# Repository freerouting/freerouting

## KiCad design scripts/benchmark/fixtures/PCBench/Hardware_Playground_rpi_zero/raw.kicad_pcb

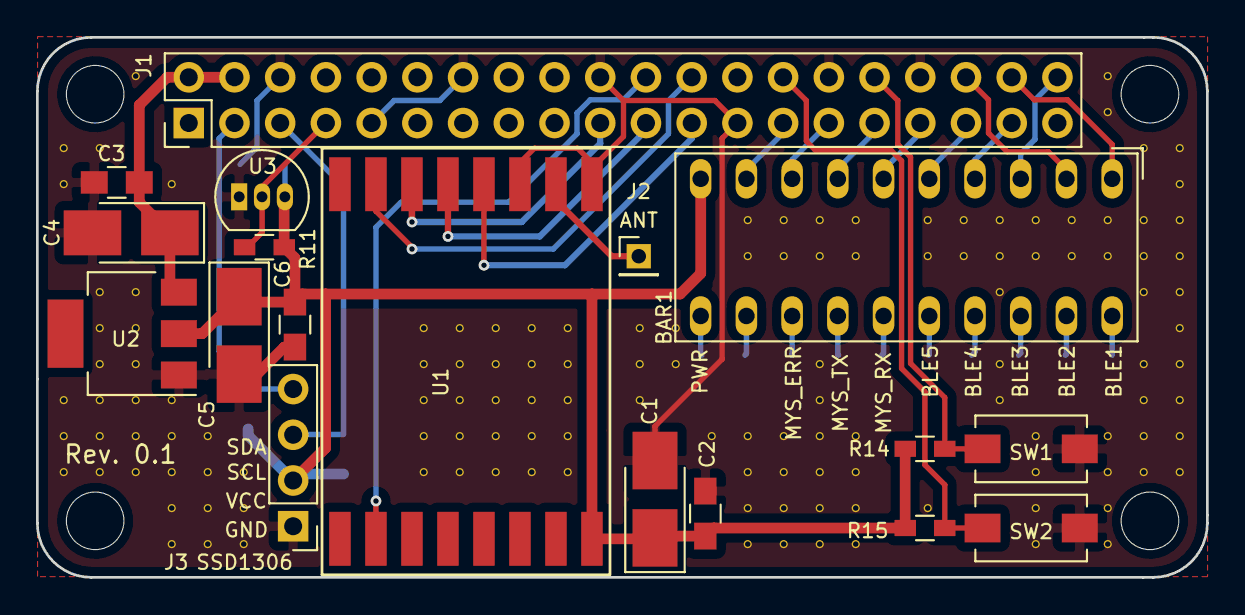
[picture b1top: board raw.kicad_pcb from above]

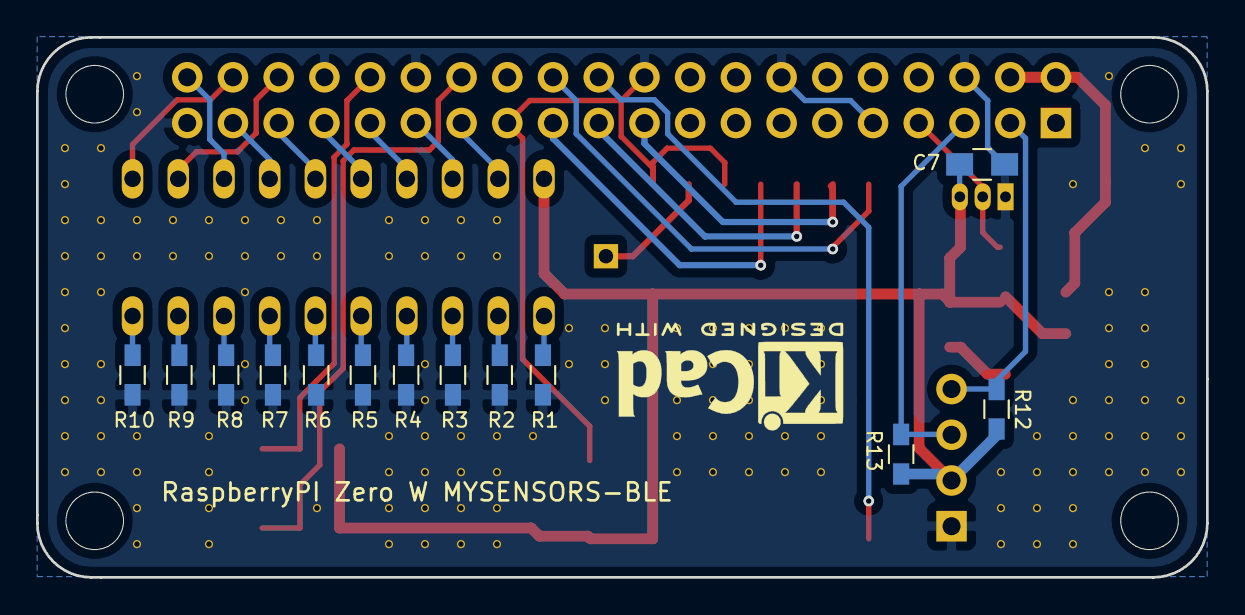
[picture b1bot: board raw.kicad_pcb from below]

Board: 2 copper layers, 65.0 x 30.0 mm, 164 parts (13 on the bottom side), 33 nets.

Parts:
BAR1: HDSP-4850_2; HDSP-4850
C1, C4, C5: 22u; CP_Tantalum_Case-B_EIA-3528-21_Hand
C2, C3, C6, C7: 100n; C_0805_HandSoldering
J1: RPI_Zero_W; Pin_Header_Straight_2x20_Pitch2.54mm
J2: ANT; Pin_Header_Straight_1x01_Pitch2.00mm
J3: SSD1306; Pin_Header_Straight_1x04_Pitch2.54mm
R1, R2, R3, R4, R5, R6, R7, R8, R9, R10: 220; R_0603_HandSoldering
R11, R12, R13: 4K7; R_0603_HandSoldering
R14, R15: 10K; R_0603_HandSoldering
SW1, SW2: BLE; SW_SPST_EVQPE1
U1: RFM69HW; RFM69HW_SMD_Handsoldering
U2: AMS1117; SOT-223
U3: DS18B20; TO-92_Inline_Narrow_Oval
V3_4, V3_5, V3_11, V3_12, V3_13, V4_4, V4_8, V4_9, V4_10, V4_11, V4_12, V4_13, V5_2, V5_8, V5_9, V5_10, V5_11, V5_12, V5_13, V6_5, V6_11, V6_12, V6_13, V6_14, V6_15, V7_12, V7_13, V7_14, V7_15, V8_13, V8_14, V8_15, V13_9, V13_10, V13_11, V13_12, V13_13, V14_9, V14_10, V14_11, V14_12, V14_13, V15_9, V15_10, V15_11, V15_12, V15_13, V16_9, V16_10, V16_11, V16_12, V16_13, V17_9, V17_10, V17_11, V17_12, V17_13, V19_9, V19_10, V19_11, V20_9, V20_10, V21_12, V22_6, V22_7, V22_12, V22_13, V22_14, V22_15, V23_6, V23_7, V23_12, V23_13, V23_14, V23_15, V24_6, V24_7, V24_10, V24_11, V24_12, V24_13, V24_14, V24_15, V25_6, V25_7, V25_12, V25_13, V25_14, V25_15, V27_6, V27_7, V27_14, V28_6, V28_7, V29_6, V29_7, V29_8, V29_10, V29_11, V30_6, V30_7, V30_12, V30_13, V30_14, V30_15, V31_6, V31_7, V32_2, V32_3, V32_6, V32_7, V32_12, V32_13, V32_14, V32_15, V33_4, V33_6, V33_7, V33_8, V33_10, V33_11, V33_12, V33_13, V34_4, V34_5, V34_6, V34_7, V34_8, V34_9, V34_10, V34_11, V34_12, V34_13: AUTO_VIA; VIA_MATRIX

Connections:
+3V3: BAR1.10, C1.1, C2.2, C5.1, C6.2, C7.1, J3.2, R11.1, R12.2, R13.2, R14.1, R15.1, U1.8, U2.2, U3.3
+5V: C3.2, C4.1, J1.2, J1.4, U2.3
/RFM69_CE: J1.22, U1.2
/RFM69_CS: J1.24, U1.15
/RFM69_MISO: J1.21, U1.13
/RFM69_MOSI: J1.19, U1.14
/RFM69_SCK: J1.23, U1.12
/SSD_SCL: J1.5, J3.3, R13.1
/SSD_SDA: J1.3, J3.4, R12.1
/SW1: J1.32, R14.2, SW1.1
/SW2: J1.28, R15.2, SW2.1
GND: C1.2, C2.1, C3.1, C4.2, C5.2, C6.1, C7.2, J1.6, J1.9, J1.14, J1.20, J1.25, J1.30, J1.34, J1.39, J3.1, R1.2, R2.2, R3.2, R4.2, R5.2, R6.2, R7.2, R8.2, R9.2, R10.2, SW1.2, SW2.2, U1.9, U1.11, U2.1, U3.1, V3_4.1, V3_5.1, V3_11.1, V3_12.1, V3_13.1, V4_4.1, V4_8.1, V4_9.1, V4_10.1, V4_11.1, V4_12.1, V4_13.1, V5_2.1, V5_8.1, V5_9.1, V5_10.1, V5_11.1, V5_12.1, V5_13.1, V6_5.1, V6_11.1, V6_12.1, V6_13.1, V6_14.1, V6_15.1, V7_12.1, V7_13.1, V7_14.1, V7_15.1, V8_13.1, V8_14.1, V8_15.1, V13_9.1, V13_10.1, V13_11.1, V13_12.1, V13_13.1, V14_9.1, V14_10.1, V14_11.1, V14_12.1, V14_13.1, V15_9.1, V15_10.1, V15_11.1, V15_12.1, V15_13.1, V16_9.1, V16_10.1, V16_11.1, V16_12.1, V16_13.1, V17_9.1, V17_10.1, V17_11.1, V17_12.1, V17_13.1, V19_9.1, V19_10.1, V19_11.1, V20_9.1, V20_10.1, V21_12.1, V22_6.1, V22_7.1, V22_12.1, V22_13.1, V22_14.1, V22_15.1, V23_6.1, V23_7.1, V23_12.1, V23_13.1, V23_14.1, V23_15.1, V24_6.1, V24_7.1, V24_10.1, V24_11.1, V24_12.1, V24_13.1, V24_14.1, V24_15.1, V25_6.1, V25_7.1, V25_12.1, V25_13.1, V25_14.1, V25_15.1, V27_6.1, V27_7.1, V27_14.1, V28_6.1, V28_7.1, V29_6.1, V29_7.1, V29_8.1, V29_10.1, V29_11.1, V30_6.1, V30_7.1, V30_12.1, V30_13.1, V30_14.1, V30_15.1, V31_6.1, V31_7.1, V32_2.1, V32_3.1, V32_6.1, V32_7.1, V32_12.1, V32_13.1, V32_14.1, V32_15.1, V33_4.1, V33_6.1, V33_7.1, V33_8.1, V33_10.1, V33_11.1, V33_12.1, V33_13.1, V34_4.1, V34_5.1, V34_6.1, V34_7.1, V34_8.1, V34_9.1, V34_10.1, V34_11.1, V34_12.1, V34_13.1
unnamed: BAR1.1, J1.38
unnamed: BAR1.2, J1.36
unnamed: BAR1.3, J1.40
unnamed: BAR1.4, J1.37
unnamed: BAR1.5, J1.35
unnamed: BAR1.6, J1.33
unnamed: BAR1.7, J1.31
unnamed: BAR1.8, J1.29
unnamed: BAR1.9, J1.27
unnamed: BAR1.11, R1.1
unnamed: BAR1.12, R2.1
unnamed: BAR1.13, R3.1
unnamed: BAR1.14, R4.1
unnamed: BAR1.15, R5.1
unnamed: BAR1.16, R6.1
unnamed: BAR1.17, R7.1
unnamed: BAR1.18, R8.1
unnamed: BAR1.19, R9.1
unnamed: BAR1.20, R10.1
unnamed: J1.7, R11.2, U3.2
unnamed: J2.1, U1.10

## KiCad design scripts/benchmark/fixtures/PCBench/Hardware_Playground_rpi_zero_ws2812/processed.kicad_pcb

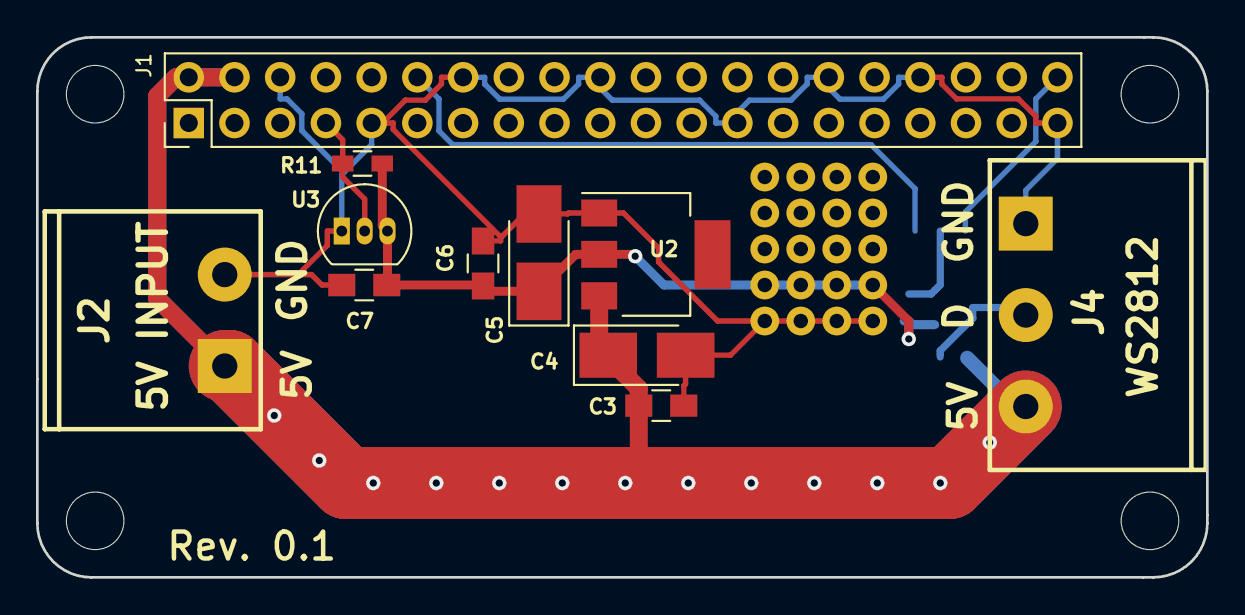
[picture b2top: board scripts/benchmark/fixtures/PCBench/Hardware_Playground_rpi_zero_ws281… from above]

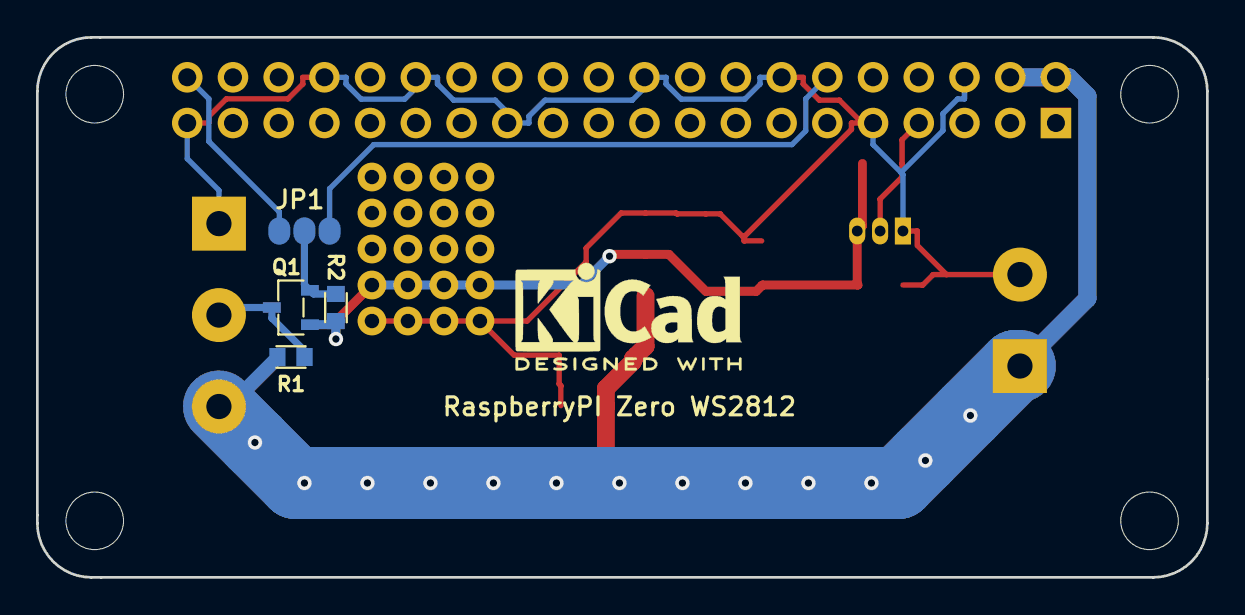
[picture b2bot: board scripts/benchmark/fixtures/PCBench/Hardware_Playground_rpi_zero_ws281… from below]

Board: 2 copper layers, 65.0 x 30.0 mm, 15 parts (4 on the bottom side), 8 nets.

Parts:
C3, C6, C7: 100n; C_0805_HandSoldering
C4, C5: 22u; CP_Tantalum_Case-B_EIA-3528-21_Hand
J1: RPI_Zero; Pin_Header_Straight_2x20_Pitch2.54mm
J2: 5V INPUT; mstba_2,5%2f2-g-5,08
J4: WS2812; mstba_2,5%2f3-g-5,08
JP1: ws2812_data_sel; 3_pin_solder_jumper_smd
Q1: BSS138; sot23
R1, R2: 10K; r_0603
R11: 4K7; R_0603_HandSoldering
U2: AMS1117; SOT-223
U3: DS18B20; TO-92_Inline_Narrow_Oval

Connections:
+3V3: C5.1, C6.2, C7.1, Q1.1, R2.2, R11.1, U2.2, U3.3
+5V: C3.2, C4.1, J1.2, J1.4, J2.1, J4.3, R1.1, U2.3
/TEMP_SENS: J1.7, R11.2, U3.2
/WS2812_DIN: JP1.2, Q1.3, R2.1
/WS2812_DOUT: J4.2, Q1.2, R1.2
/WS2812_PCM: J1.40, JP1.1
/WS2812_PWM: J1.12, JP1.3
GND: C3.1, C4.2, C5.2, C6.1, C7.2, J1.6, J1.9, J1.14, J1.20, J1.25, J1.30, J1.34, J1.39, J2.2, J4.1, U2.1, U3.1

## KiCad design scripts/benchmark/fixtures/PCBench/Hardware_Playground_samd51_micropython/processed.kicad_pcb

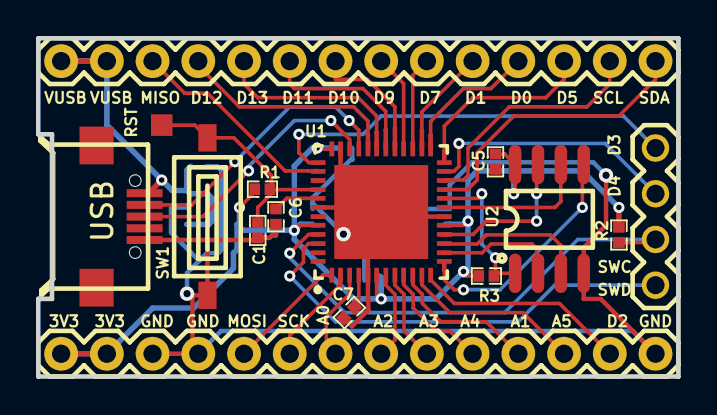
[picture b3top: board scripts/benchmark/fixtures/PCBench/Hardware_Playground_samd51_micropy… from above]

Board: 2 copper layers, 35.6 x 18.8 mm, 21 parts (0 on the bottom side), 39 nets.

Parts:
C1, C2, C3, C4, C7, C8, C9, C10: 1uF; 0402
C5: 100nF; 0402
C6: 10uF; 0402
H2: Header-Male-2.54_1x4; 210S-1X4P
JP1, JP2: M14; 1X14
R1: 10K; 0402
R2: 2K2; 0402
R3: 100K; 0402
SW1: RESET; SWITCH-3X6X2.5_SMD
U1: ATSAMD51G19A-MU; 48QFN7X7
U2: IS25LP016D-JBLE; SOIC-8
U3: AP2112K-3.3TRG1; SOT-25
USB: Micro USB-B 5P_C40942; MICRO-USB-12

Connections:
+3V3: C3.2, C4.1, C5.2, C8.1, C9.1, C10.2, JP2.13, JP2.14, R1.2, R2.2, R3.2, U1.6, U1.17, U1.36, U1.44, U2.8, U3.5
A0: JP2.8, U1.3
A1: JP2.4, U1.10
A2: JP2.7, U1.7
A3: JP2.6, U1.8
A4: JP2.5, U1.9
A5: JP2.3, U1.11
AREF: C7.1, U1.4
D2: JP2.2, U1.12
D3: H2.4, U1.37
D4: H2.3, U1.23
D5: JP1.12, U1.24
D7: JP1.9, U1.27
D9: JP1.8, U1.28
D10: JP1.7, U1.29
D11: JP1.6, U1.30
D12: JP1.4, U1.32
D13: JP1.5, U1.31
D+: U1.34, USB.3
D-: U1.33, USB.2
GND: C1.1, C2.2, C3.1, C4.2, C6.1, C7.2, C8.2, C9.2, C10.1, JP2.1, JP2.11, JP2.12, SW1.1, U1.5, U1.18, U1.35, U1.42, U1.49, U2.4, U3.2, USB.5
MISO: JP1.3, U1.38
MOSI: JP2.10, U1.1
QSPI_CS: R3.1, U1.20, U2.1
QSPI_DAT0: U1.13, U2.5
QSPI_DAT1: U1.14, U2.2
QSPI_DAT2: U1.15, U2.3
QSPI_DAT3: U1.16, U2.7
QSPI_SCK: U1.19, U2.6
RST: C1.2, R1.1, SW1.2, U1.40
RX_D0: JP1.11, U1.25
SCK: JP2.9, U1.2
SCL: JP1.13, U1.22
SDA: JP1.14, U1.21
SWCLK: H2.2, R2.1, U1.45
SWDIO: H2.1, U1.46
TX_D1: JP1.10, U1.26
U1_41: C6.2, U1.41
VUSB: C2.1, JP1.1, JP1.2, U3.1, U3.3, USB.1
